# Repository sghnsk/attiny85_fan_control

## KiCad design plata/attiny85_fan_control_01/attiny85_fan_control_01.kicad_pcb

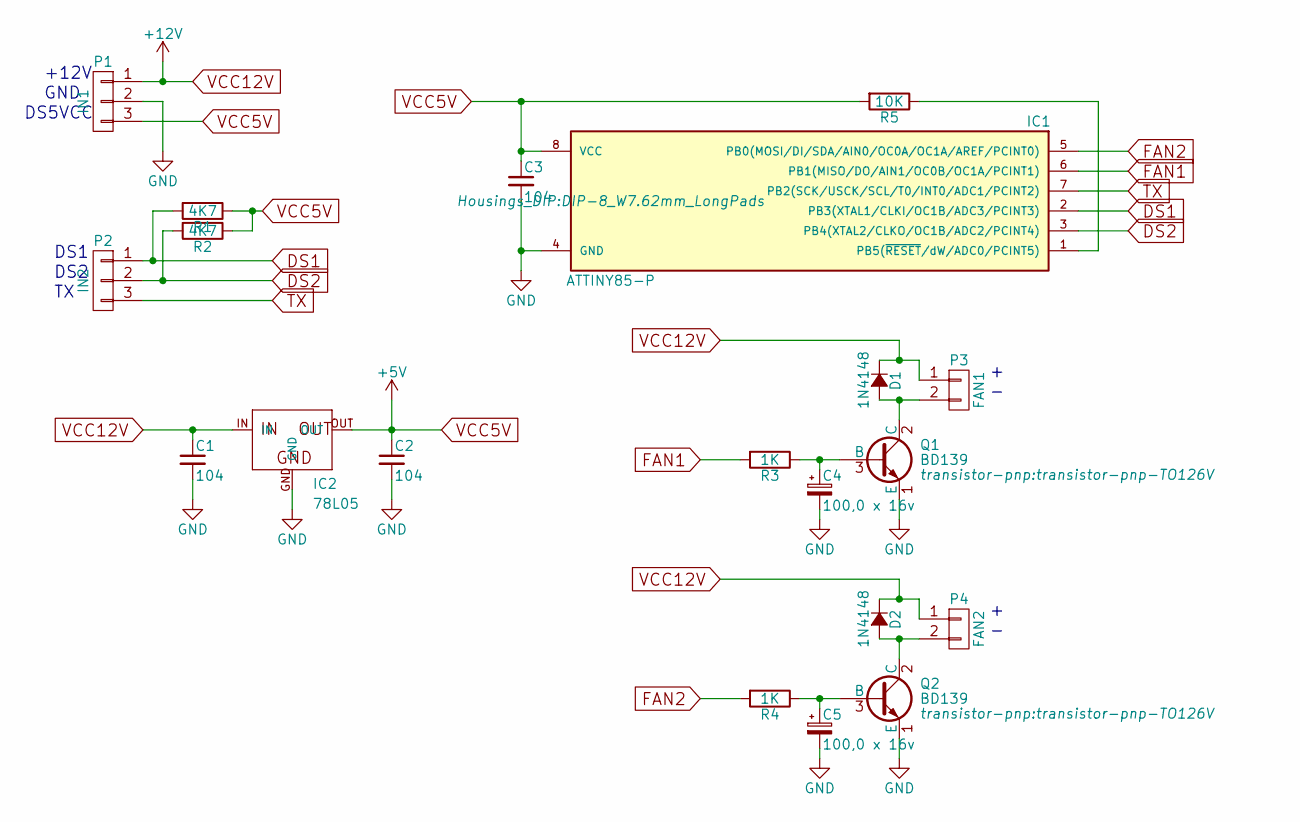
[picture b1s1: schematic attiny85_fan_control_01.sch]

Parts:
C1, C2, C3: 104; C_Disc_D3_P2.5
C4, C5: 100,0 x 16v; C_Radial_D6.3_L11.2_P2.5
D1, D2: 1N4148; diode-DO34-5
IC1: ATTINY85-P; DIP-8_W7.62mm_LongPads
IC2: 78L05; v-reg-78LXX
P1: IN1; DG350-3.5_3pin
P2: IN2; DG350-3.5_3pin
P3: FAN1; DG350-3.5_2pin
P4: FAN2; DG350-3.5_2pin
Q1, Q2: BD139; transistor-pnp-TO126V
R1, R2: 4K7; R1
R3: 1K; R3
R4: 1K; R1
R5: 10K; R1

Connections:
DS1: IC1.2 (PB3(XTAL1/CLKI/OC1B/ADC3/PCINT3)), P2.1, R1.2
DS2: IC1.3 (PB4(XTAL2/CLKO/OC1B/ADC2/PCINT4)), P2.2, R2.2
FAN1: IC1.6 (PB1(MISO/DO/AIN1/OC0B/OC1A/PCINT1)), R3.2
FAN2: IC1.5 (PB0(MOSI/DI/SDA/AIN0/OC0A/OC1A/AREF/PCI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), R4.2
GND: C1.2, C2.2, C3.2, C4.2, C5.2, IC1.4 (GND), IC2.GND, P1.2, Q1.1 (E), Q2.1 (E)
unnamed: C4.1, Q1.3 (B), R3.1
unnamed: C5.1, Q2.3 (B), R4.1
unnamed: D1.2 (A), P3.2, Q1.2 (C)
unnamed: D2.2 (A), P4.2, Q2.2 (C)
unnamed: IC1.1 (PB5(~RESET~/dW/ADC0/PCINT5)), R5.1
TX: IC1.7 (PB2(SCK/USCK/SCL/T0/INT0/ADC1/PCINT2)), P2.3
VCC5V: C2.1, C3.1, IC1.8 (VCC), IC2.OUT, P1.3, R1.1, R2.1, R5.2
VCC12V: C1.1, D1.1 (C), D2.1 (C), IC2.IN, P1.1, P3.1, P4.1

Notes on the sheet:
DS1
DS2
+12V
DS5VCC
GND

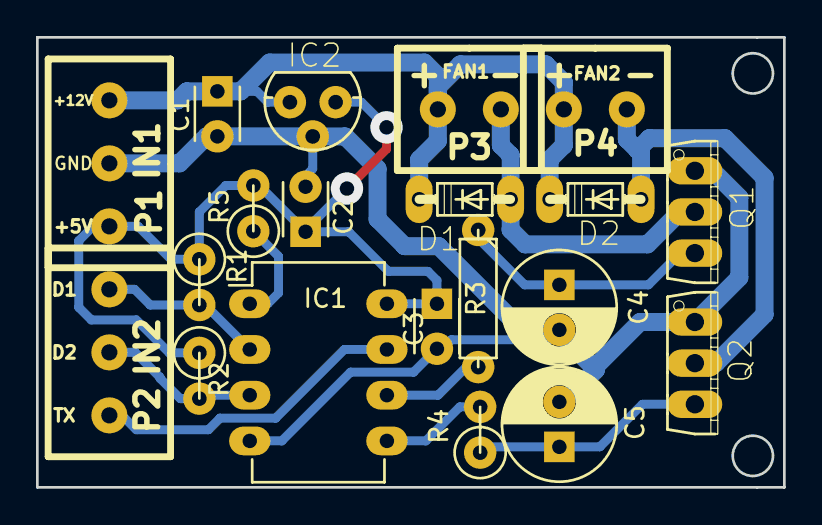
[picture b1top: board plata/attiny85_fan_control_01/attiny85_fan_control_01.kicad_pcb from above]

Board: 2 copper layers, 41.5 x 25.0 mm, 20 parts (0 on the bottom side), 13 nets.

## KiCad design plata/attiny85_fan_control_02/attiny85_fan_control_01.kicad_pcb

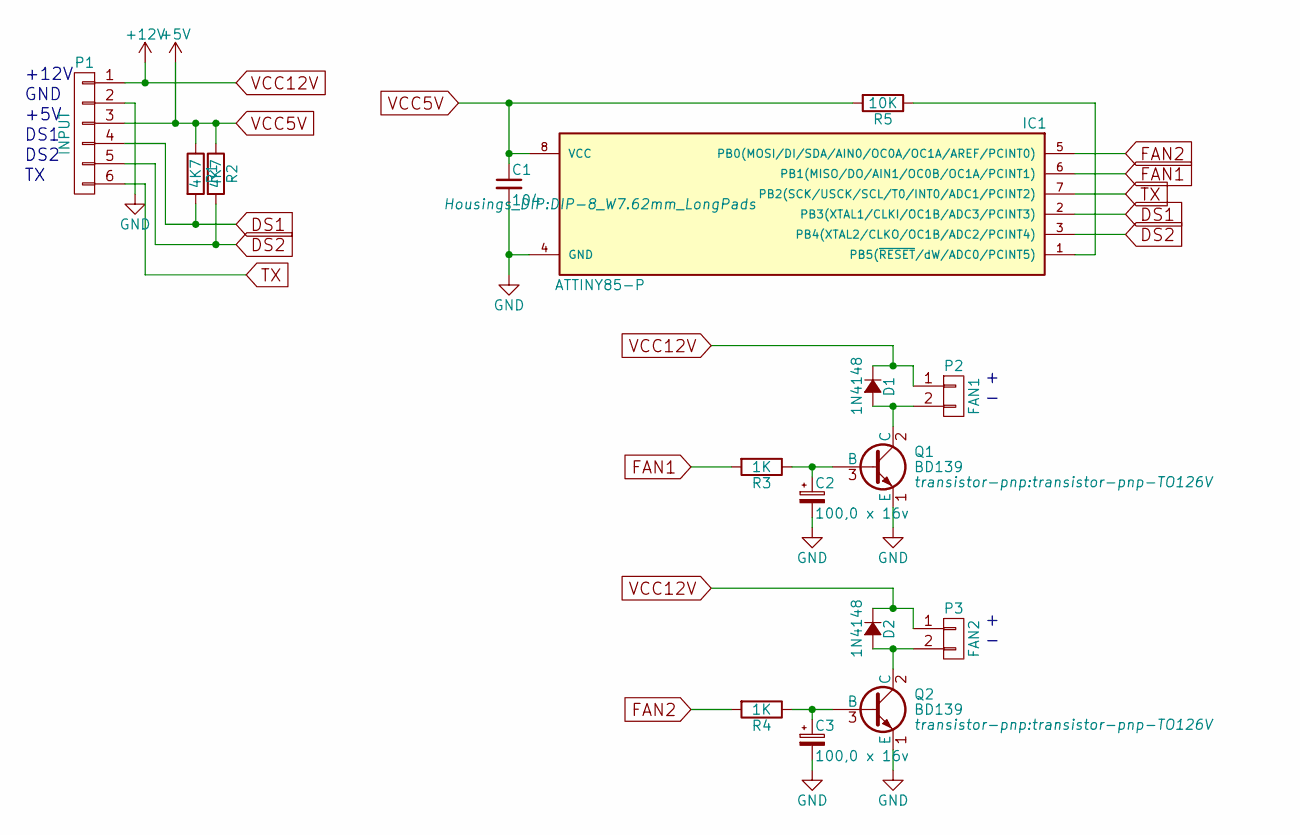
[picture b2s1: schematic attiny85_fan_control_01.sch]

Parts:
C1: 104; C_Disc_D3_P2.5
C2, C3: 100,0 x 16v; C_Radial_D6.3_L11.2_P2.5
D1, D2: 1N4148; diode-DO34-5
IC1: ATTINY85-P; DIP-8_W7.62mm_LongPads
P1: INPUT; Pin_Header_Straight_1x06
P2: FAN1; Pin_Header_Straight_1x02
P3: FAN2; Pin_Header_Straight_1x02
Q1, Q2: BD139; transistor-pnp-TO126V
R1, R2: 4K7; R1
R3: 1K; R3
R4: 1K; R1
R5: 10K; R1

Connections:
DS1: IC1.2 (PB3(XTAL1/CLKI/OC1B/ADC3/PCINT3)), P1.4, R1.2
DS2: IC1.3 (PB4(XTAL2/CLKO/OC1B/ADC2/PCINT4)), P1.5, R2.2
FAN1: IC1.6 (PB1(MISO/DO/AIN1/OC0B/OC1A/PCINT1)), R3.2
FAN2: IC1.5 (PB0(MOSI/DI/SDA/AIN0/OC0A/OC1A/AREF/PCI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), R4.2
GND: C1.2, C2.2, C3.2, IC1.4 (GND), P1.2, Q1.1 (E), Q2.1 (E)
unnamed: C2.1, Q1.3 (B), R3.1
unnamed: C3.1, Q2.3 (B), R4.1
unnamed: D1.2 (A), P2.2, Q1.2 (C)
unnamed: D2.2 (A), P3.2, Q2.2 (C)
unnamed: IC1.1 (PB5(~RESET~/dW/ADC0/PCINT5)), R5.1
TX: IC1.7 (PB2(SCK/USCK/SCL/T0/INT0/ADC1/PCINT2)), P1.6
VCC5V: C1.1, IC1.8 (VCC), P1.3, R1.1, R2.1, R5.2
VCC12V: D1.1 (C), D2.1 (C), P1.1, P2.1, P3.1

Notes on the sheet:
DS1
DS2
+12V
+5V
GND

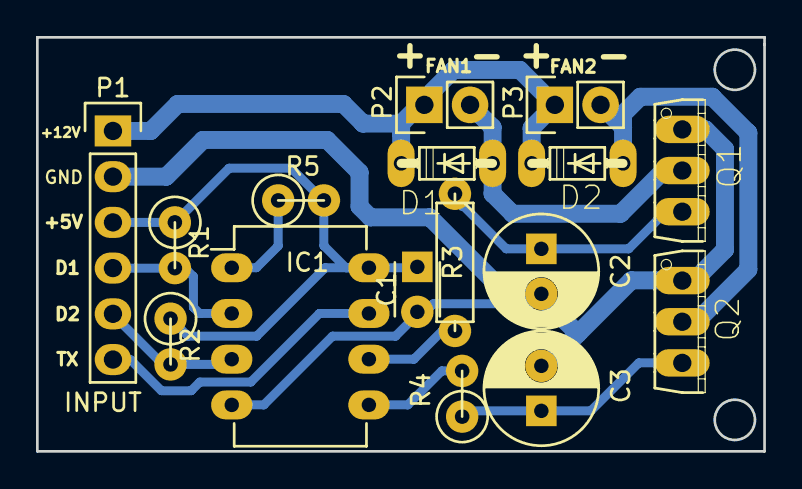
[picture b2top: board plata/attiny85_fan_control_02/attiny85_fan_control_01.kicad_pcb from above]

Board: 2 copper layers, 40.4 x 23.0 mm, 16 parts (0 on the bottom side), 13 nets.

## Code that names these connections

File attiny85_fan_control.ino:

// OneWire DS18B20 Temperature Switch on ATtiny85
// http://www.nerdkits.com/forum/thread/2849/
// source: http://www.electroschematics.com/9540/arduino-fan-speed-controlled-temperature/


#include <OneWire.h>


#include <SoftwareSerial.h>
#define SERIAL_RX -1
#define SERIAL_TX 2
SoftwareSerial mySerial(SERIAL_RX, SERIAL_TX); // RX, TX

// fan switch temperatures
#define TEMP_MIN 40 // C°
#define TEMP_MAX 100 // C°
// #define FT_START 3000 // msec
#define FT_START 5000 // msec
#define DELAY_TIMEOUT	1000
// #define PWM_MIN 70 // минимальное значение pwm
// #define PWM_MIN 65 // минимальное значение pwm
// #define PWM_MIN 55 // минимальное значение pwm
#define PWM_MIN_1 35 // минимальное значение pwm
#define PWM_MAX_1 255 // максимальное значение pwm
#define PWM_MIN_2 36 // минимальное значение pwm
#define PWM_MAX_2 255 // максимальное значение pwm
// pins
// ATMEL ATTINY45 / ARDUINO
//                           +-\/-+
//  Ain0       (D  5)  PB5  1|    |8   VCC
//  Ain3       (D  3)  PB3  2|    |7   PB2  (D  2)  INT0  Ain1
//  Ain2       (D  4)  PB4  3|    |6   PB1  (D  1)        pwm1
//                     GND  4|    |5   PB0  (D  0)        pwm0
//                           +----+
#define DS_1 3
#define DS_2 4
// #define STATUS_LED  2
#define FAN_1 1
#define FAN_2 0
  
OneWire ds1(DS_1);  // Dallas one wire data buss pin, a 4.7K resistor pullup is needed
OneWire ds2(DS_2);  // Dallas one wire data buss pin, a 4.7K resistor pullup is needed

 
void setup() {
	mySerial.begin(9600);
	
	
	pinMode(FAN_1, OUTPUT);
    pinMode(FAN_2, OUTPUT);
    
	// pinMode(STATUS_LED, OUTPUT);

	// delay(1000);
	// расскрутить после включения на максимум на время FT_START и после выставить минимальную скорость
	analogWrite(FAN_1, PWM_MAX_1);
	analogWrite(FAN_2, PWM_MAX_2);
	delay(FT_START);
	analogWrite(FAN_1, PWM_MIN_1);
	analogWrite(FAN_2, PWM_MIN_2);
}

void loop() {
	
	delay(DELAY_TIMEOUT);
	mySerial.print(F("ds1"));
	int temp1 = GetMaxTemperature(&ds1);
	mySerial.print(F("ds2"));
	int temp2 = GetMaxTemperature(&ds2);
	int maxTemp = max(temp1, temp2);
	
	mySerial.print(F("fan1;"));
	SetFanSpeedWithTemp(FAN_1, maxTemp, PWM_MIN_1, PWM_MAX_1);
    mySerial.print(F("fan2;"));
	SetFanSpeedWithTemp(FAN_2, maxTemp, PWM_MIN_2, PWM_MAX_2);
}


int16_t GetMaxTemperature(OneWire *Sensor) {
	byte data[12];
	int16_t raw = 0;
	int16_t celsius = 0;
	int16_t maxValue = 0;
	
	byte addr[8];
	
	Sensor->reset_search();
	
	while(Sensor->search(addr)) {
		Sensor->reset();       // reset one wire buss
		Sensor->select(addr);
		Sensor->write(0x44);   // start conversion
		// delay(1000);                     // wait for the conversion 
		Sensor->reset();
		// Sensor->skip();
		Sensor->select(addr);
		Sensor->write(0xBE);   // Read Scratchpad
		for (byte i = 0; i < 9; i++) {       // 9 bytes
			data[i] = Sensor->read();
		} 
		// Convert the data to actual temperature
		raw = (data[1] << 8) | data[0];
		celsius = raw / 16;
		
		mySerial.print(F(";"));
		printAddress(addr);
		mySerial.print(F(";"));
		mySerial.print(celsius);
		
		// обновить максимальное значение
		if (celsius > maxValue) {
			maxValue = celsius;
		}
	}
	Sensor->reset_search();
	
	mySerial.println(F(""));
	
	return maxValue;
}

void printAddress(byte *deviceAddress) {
  for (uint8_t i = 0; i < 8; i++)
  {
    // zero pad the address if necessary
    if (deviceAddress[i] < 16) Serial.print("0");
    mySerial.print(deviceAddress[i], HEX);
  }
}

void SetFanSpeedWithTemp(int fanPin, int temp, int pwmMin, int pwmMax) {
	int fanSpeed = pwmMin;
	// if(temp < TEMP_MIN) {   // if temp is lower than minimum temp
		// fanSpeed = 0;      // fan is not spinning
		// digitalWrite(fanPin, LOW);       
	// } 
	if(temp < TEMP_MIN) {
		analogWrite(fanPin, pwmMin);       
	} 
	if((temp >= TEMP_MIN) && (temp <= TEMP_MAX)) {  // if temperature is higher than minimum temp
		fanSpeed = map(temp, TEMP_MIN, TEMP_MAX, pwmMin, pwmMax); // the actual speed of fan
		analogWrite(fanPin, fanSpeed);  // spin the fan at the fanSpeed speed
	} 

	if(temp > TEMP_MAX) {        // if temp is higher than tempMax
		fanSpeed = pwmMax;
	}
	// if(temp > TEMP_MAX) {        // if temp is higher than tempMax
		// digitalWrite(STATUS_LED, HIGH);  // turn on led 
	// } else {                    // else turn of led
		// digitalWrite(STATUS_LED, LOW); 
	// }
	int fanPrecent = map(fanSpeed, pwmMin, pwmMax, 0, 100);
	
	mySerial.print(temp);      // display the temperature
	mySerial.print(F(";C;"));
	mySerial.print(fanPrecent);    // display the fan speed
	mySerial.print(F(";%;"));
	mySerial.print(fanSpeed);    // display the fan speed
	mySerial.println(F(";pwm"));
}

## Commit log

2019-07-16 IniInitial commit
